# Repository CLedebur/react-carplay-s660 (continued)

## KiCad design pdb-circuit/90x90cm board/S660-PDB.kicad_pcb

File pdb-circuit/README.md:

# KiCad MCP workflow

Open the repository root in VS Code. The local `.vscode/mcp.json` connects
GitHub Copilot Agent mode to the separately installed KiCAD MCP server.
Use **MCP: List Servers** in the Command Palette to start `KiCAD-MCP-Server`
and confirm its tools are available, accepting VS Code's trust prompt if shown.

For a new checkout, copy `.vscode/mcp.example.json` to `.vscode/mcp.json`.
The example assumes the built `KiCAD-MCP-Server` repository is a sibling of
this repository and uses macOS KiCad Python paths. Adjust the Node command,
server entrypoint, `KICAD_PYTHON`, and `PYTHONPATH` to match your installation.
The active configuration is ignored by Git; the example is shared.

The local setup uses `.venv-kicad`, created with KiCad's bundled Python and
`--system-site-packages` so it can import `pcbnew`. To recreate it on macOS:

```bash
/Applications/KiCad/KiCad.app/Contents/Frameworks/Python.framework/Versions/Current/bin/python3 -m venv --system-site-packages .venv-kicad
.venv-kicad/bin/python3 -m pip install -r ../KiCAD-MCP-Server/requirements.txt
```

Set `KICAD_PYTHON` in your local `.vscode/mcp.json` to
`${workspaceFolder}/.venv-kicad/bin/python3` when using this environment.

Setup reference:
[KiCAD MCP Server — GitHub Copilot (VS Code)](https://github.com/mixelpixx/KiCAD-MCP-Server/blob/main/README.md#github-copilot-vs-code).

## Existing designs

Specify the exact design before asking the assistant to open or edit it:

| Directory | Project | Board | Schematic |
| --- | --- | --- | --- |
| `90x90cm board` | `S660-PDB.kicad_pro` | `S660-PDB.kicad_pcb` | `S660-PDB.kicad_sch` |
| `109x49cm board` | `S660-PCB-long.kicad_pro` | `S660-PCB-long.kicad_pcb` | `S660-PCB-long.kicad_sch` |
| `smt board` | `S660-PCB-long.kicad_pro` | `S660-PCB-long.kicad_pcb` | `S660-PCB-long.kicad_sch` |
| `smt board` | `S660-PCB-SMT-two-sided.kicad_pro` | `S660-PCB-SMT-two-sided.kicad_pcb` | No matching schematic file |

Example first prompt:

> Use the KiCad MCP tools to open `pdb-circuit/90x90cm board/S660-PDB.kicad_pro`
> with its absolute workspace path. Inspect the board and summarize its
> components, dimensions, and design-rule violations without changing it.

Discover available operations with `search_tools` or `get_category_tools`
before selecting a tool. Open and inspect the chosen design, create a checkpoint
before substantial changes, then save and run the relevant schematic ERC or PCB
DRC checks. Review any unresolved violations before exporting manufacturing files.
Coordinate file edits with the MCP session: close the project before editing its
files externally, then reopen it to avoid saving stale in-memory state.

The configuration leaves automatic GUI launch and development session logging
disabled. To use live PCB interaction, launch KiCad yourself and enable its IPC
API server in Preferences > Plugins. File-based operation does not require the GUI.

This VS Code configuration applies to Copilot. Other MCP clients need their own
server registration; it does not register tools in an already running Codex task.

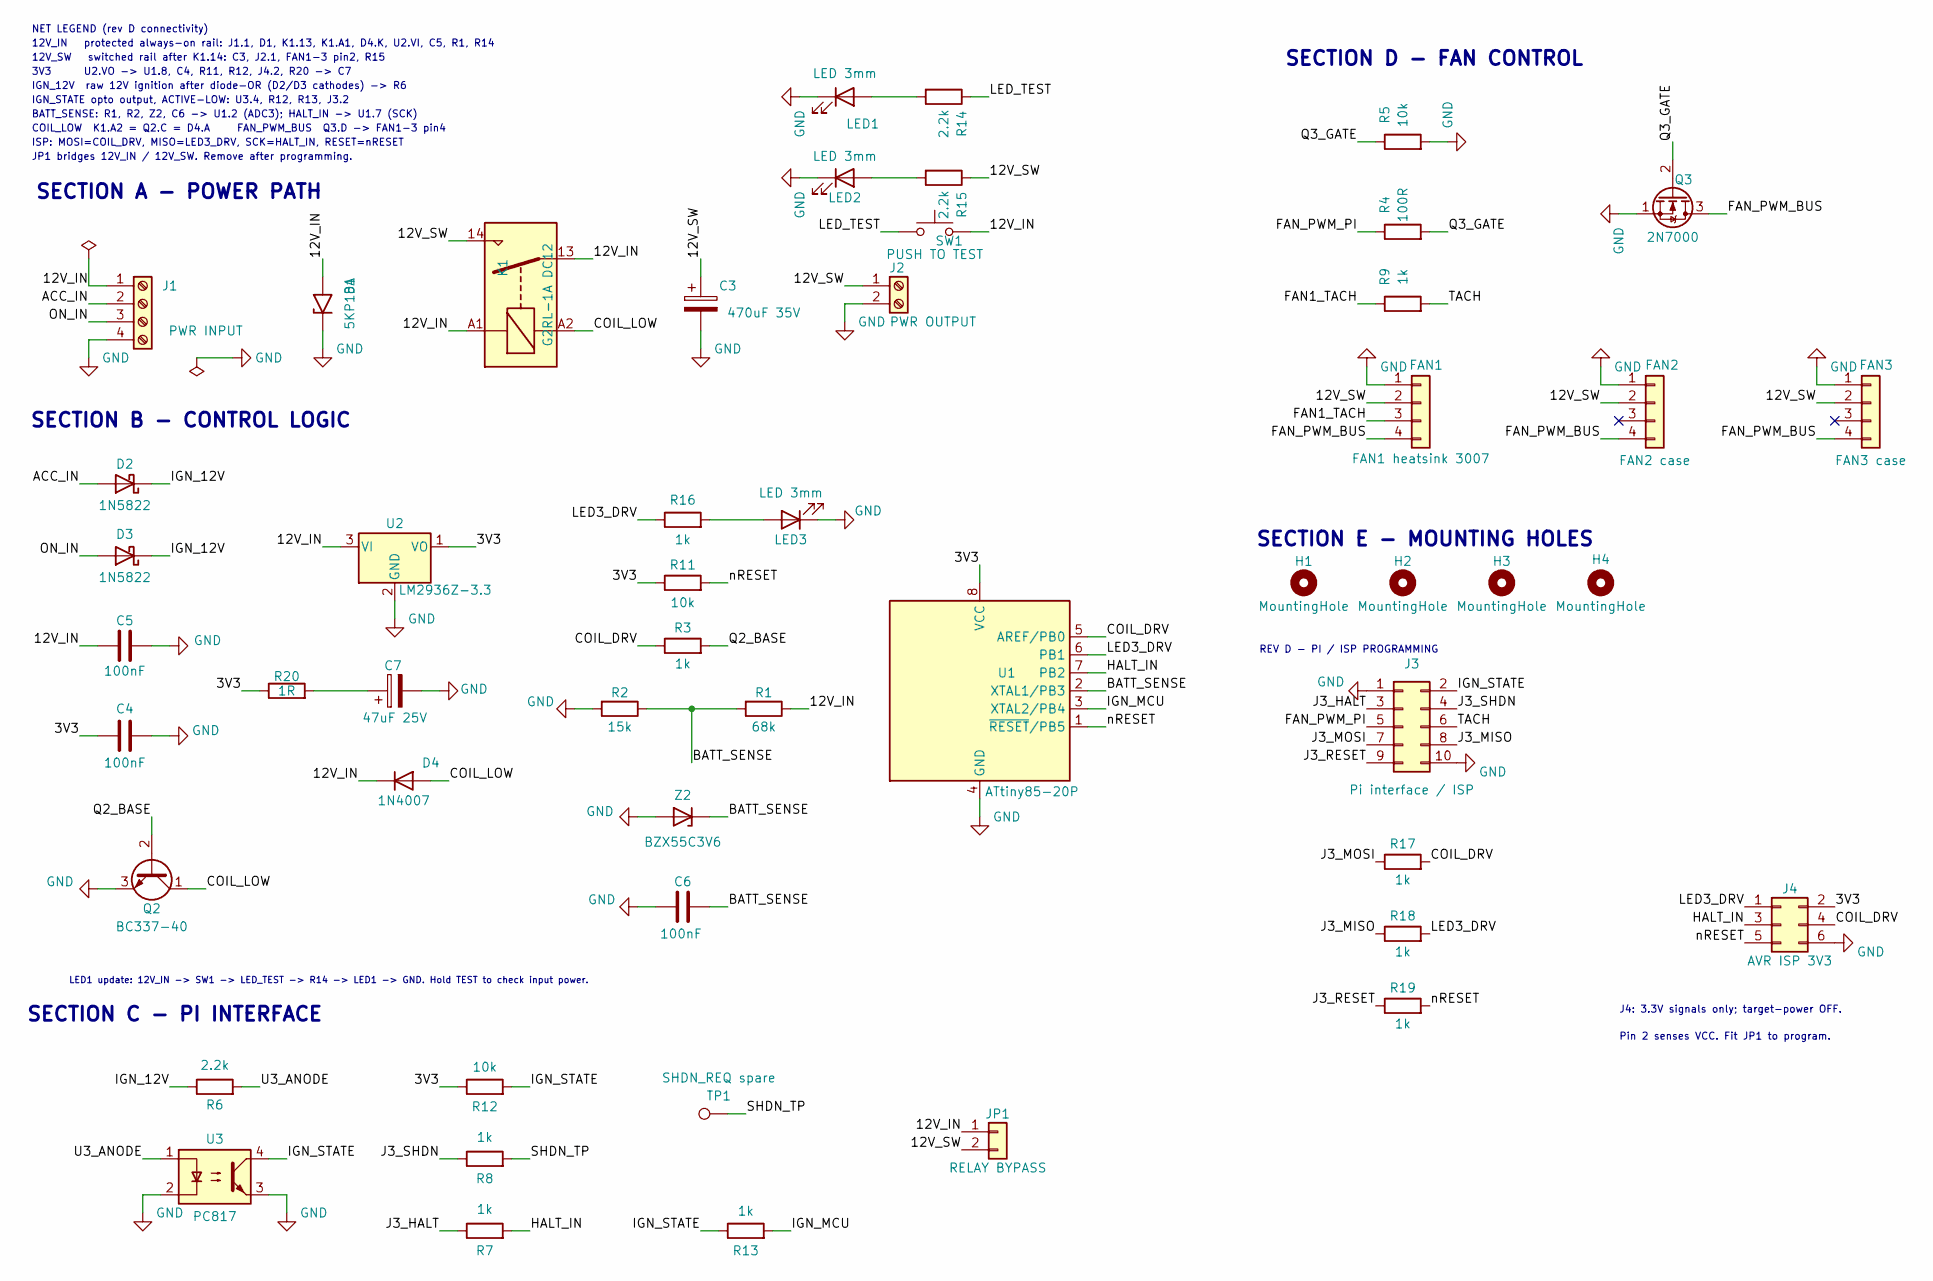
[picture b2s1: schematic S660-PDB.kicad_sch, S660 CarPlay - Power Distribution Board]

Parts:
C3: 470uF 35V; CP_Radial_D10.0mm_P5.00mm; MPN EEUFR1V471; LCSC C178715
C4, C5, C6: 100nF; C_Disc_D5.0mm_W2.5mm_P5.00mm; MPN FG28X7R1H104KNT00; LCSC C448595
C7: 47uF 25V; CP_Radial_D5.0mm_P2.00mm; MPN EEUFR1E470; LCSC C407893
D1: 5KP18A; D_P600_R-6_P20.00mm_Horizontal; MPN 5KP18A
D2, D3: 1N5822; D_Multicomp_1N5822_DO27_P15.24mm; MPN 1N5822; Farnell 4050109
D4: 1N4007; D_DO-41_SOD81_P10.16mm_Horizontal; MPN 1N4007-E3/54
FAN1: FAN1 heatsink 3007; PinHeader_1x04_P2.54mm_Vertical; MPN TSW-104-07-G-S
FAN2: FAN2 case; PinHeader_1x04_P2.54mm_Vertical; MPN TSW-104-07-G-S
FAN3: FAN3 case; PinHeader_1x04_P2.54mm_Vertical; MPN TSW-104-07-G-S
H1, H2, H3, H4: MountingHole; MountingHole_3.2mm_M3
J1: PWR INPUT; PhoenixContact_MC_1,5_4-G-5.08_1x04_P5.08mm_Horizontal; MPN 1836202; LCSC C5444352
J2: PWR OUTPUT; PhoenixContact_MC_1,5_2-G-5.08_1x02_P5.08mm_Horizontal; MPN 1836189; LCSC C5355140
J3: Pi interface / ISP; PinHeader_2x05_P2.54mm_Vertical; MPN TSW-105-07-G-D
J4: AVR ISP 3V3; PinHeader_2x03_P2.54mm_Vertical; MPN TSW-103-07-G-D
JP1: RELAY BYPASS; Phoenix_MKDS_1_2_3.5_1751248; MPN 1751248; LCSC C89122
K1: G2RL-1A DC12; Relay_SPST_Omron_G2RL-1A; MPN G2RL-1A DC12; LCSC C1524657
LED1, LED2, LED3: LED 3mm; LED_D3.0mm; MPN WP3A8ID
Q2: BC337-40; TO-92_Inline_Wide; MPN BC337-40
Q3: 2N7000; TO-92_Inline_Wide; MPN 2N7000
R1: 68k; R_Axial_DIN0207_L6.3mm_D2.5mm_P10.16mm_Horizontal; MPN MFR-25FBF52-68K
R2: 15k; R_Axial_DIN0207_L6.3mm_D2.5mm_P10.16mm_Horizontal; MPN MFR-25FBF52-15K; LCSC C3556390
R3, R7, R8, R9, R13, R16, R17, R18, R19: 1k; R_Axial_DIN0207_L6.3mm_D2.5mm_P10.16mm_Horizontal; MPN MFR-25FBF52-1K; LCSC C1364484
R4: 100R; R_Axial_DIN0207_L6.3mm_D2.5mm_P10.16mm_Horizontal; MPN MFR-25FBF52-100R
R5, R11, R12: 10k; R_Axial_DIN0207_L6.3mm_D2.5mm_P10.16mm_Horizontal; MPN MFR-25FBF52-10K; LCSC C1519255
R6, R14, R15: 2.2k; R_Axial_DIN0207_L6.3mm_D2.5mm_P10.16mm_Horizontal; MPN MFR-25FBF52-2K2
R20: 1R; R_Axial_DIN0207_L6.3mm_D2.5mm_P10.16mm_Horizontal; Power Rating 0.6W; Tolerance 1%; MPN MRS25000C1008FCT00
SW1: PUSH TO TEST; SW_PUSH_6mm_H4.3mm; MPN B3F-1000; LCSC C93157
TP1: SHDN_REQ spare; TestPoint_Pad_D1.5mm
U1: ATtiny85-20P; DIP-8_W7.62mm; MPN ATTINY85-20PU; LCSC C965497
U2: LM2936Z-3.3; TO-92_Inline_Wide; MPN LM2936Z-3.3/NOPB
U3: PC817; DIP-4_W7.62mm; MPN ISP817X
Z2: BZX55C3V6; D_DO-35_SOD27_P7.62mm_Horizontal; MPN BZX55C3V6-TAP

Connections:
/3V3: C4.1, J4.2, R11.1, R12.1, R20.1, U1.8 (VCC), U2.1 (VO)
/12V_SW: C3.1, FAN1.2, FAN2.2, FAN3.2, J2.1, JP1.2, K1.14, R15.1
/ACC_IN: D2.2 (A), J1.2
/BATT_SENSE: C6.1, R1.2, R2.1, U1.2 (XTAL1/PB3), Z2.1 (K)
/COIL_DRV: J4.4, R3.1, R17.2, U1.5 (AREF/PB0)
/COIL_LOW: D4.2 (A), K1.A2, Q2.1 (C)
/FAN1_TACH: FAN1.3, R9.1
/FAN_PWM_BUS: FAN1.4, FAN2.4, FAN3.4, Q3.3 (D)
/FAN_PWM_PI: J3.5, R4.1
/HALT_IN: J4.3, R7.2, U1.7 (PB2)
/IGN_12V: D2.1 (K), D3.1 (K), R6.1
/IGN_MCU: R13.2, U1.3 (XTAL2/PB4)
/IGN_STATE: J3.2, R12.2, R13.1, U3.4
/J3_HALT: J3.3, R7.1
/J3_MISO: J3.8, R18.1
/J3_MOSI: J3.7, R17.1
/J3_RESET: J3.9, R19.1
/J3_SHDN: J3.4, R8.1
/LED3_DRV: J4.1, R16.1, R18.2, U1.6 (PB1)
/LED_TEST: R14.1, SW1.1
/ON_IN: D3.2 (A), J1.3
/Q2_BASE: Q2.2 (B), R3.2
/Q3_GATE: Q3.2 (G), R4.2, R5.1
/SHDN_TP: R8.2, TP1.1 (1_1)
/TACH: J3.6, R9.2
/U3_ANODE: R6.2, U3.1
/nRESET: J4.5, R11.2, R19.2, U1.1 (~RESET/PB5)
unnamed: C7.1, R20.2
unnamed: LED1.2 (A), R14.2
unnamed: LED2.2 (A), R15.2
unnamed: LED3.2 (A), R16.2

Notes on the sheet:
REV D - PI / ISP PROGRAMMING
LED1 update: 12V_IN -> SW1 -> LED_TEST -> R14 -> LED1 -> GND. Hold TEST to check input power.
SECTION E - MOUNTING HOLES
JP1 bridges 12V_IN / 12V_SW. Remove after programming.
Pin 2 senses VCC. Fit JP1 to program.
SECTION C - PI INTERFACE
SECTION A - POWER PATH
SECTION D - FAN CONTROL
COIL_LOW K1.A2 = Q2.C = D4.A FAN_PWM_BUS Q3.D -> FAN1-3 pin4
ISP: MOSI=COIL_DRV, MISO=LED3_DRV, SCK=HALT_IN, RESET=nRESET
BATT_SENSE: R1, R2, Z2, C6 -> U1.2 (ADC3); HALT_IN -> U1.7 (SCK)
12V_SW switched rail after K1.14: C3, J2.1, FAN1-3 pin2, R15
12V_IN protected always-on rail: J1.1, D1, K1.13, K1.A1, D4.K, U2.VI, C5, R1, R14
NET LEGEND (rev D connectivity)
IGN_STATE opto output, ACTIVE-LOW: U3.4, R12, R13, J3.2
IGN_12V raw 12V ignition after diode-OR (D2/D3 cathodes) -> R6
SECTION B - CONTROL LOGIC
3V3 U2.VO -> U1.8, C4, R11, R12, J4.2, R20 -> C7
J4: 3.3V signals only; target-power OFF.

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
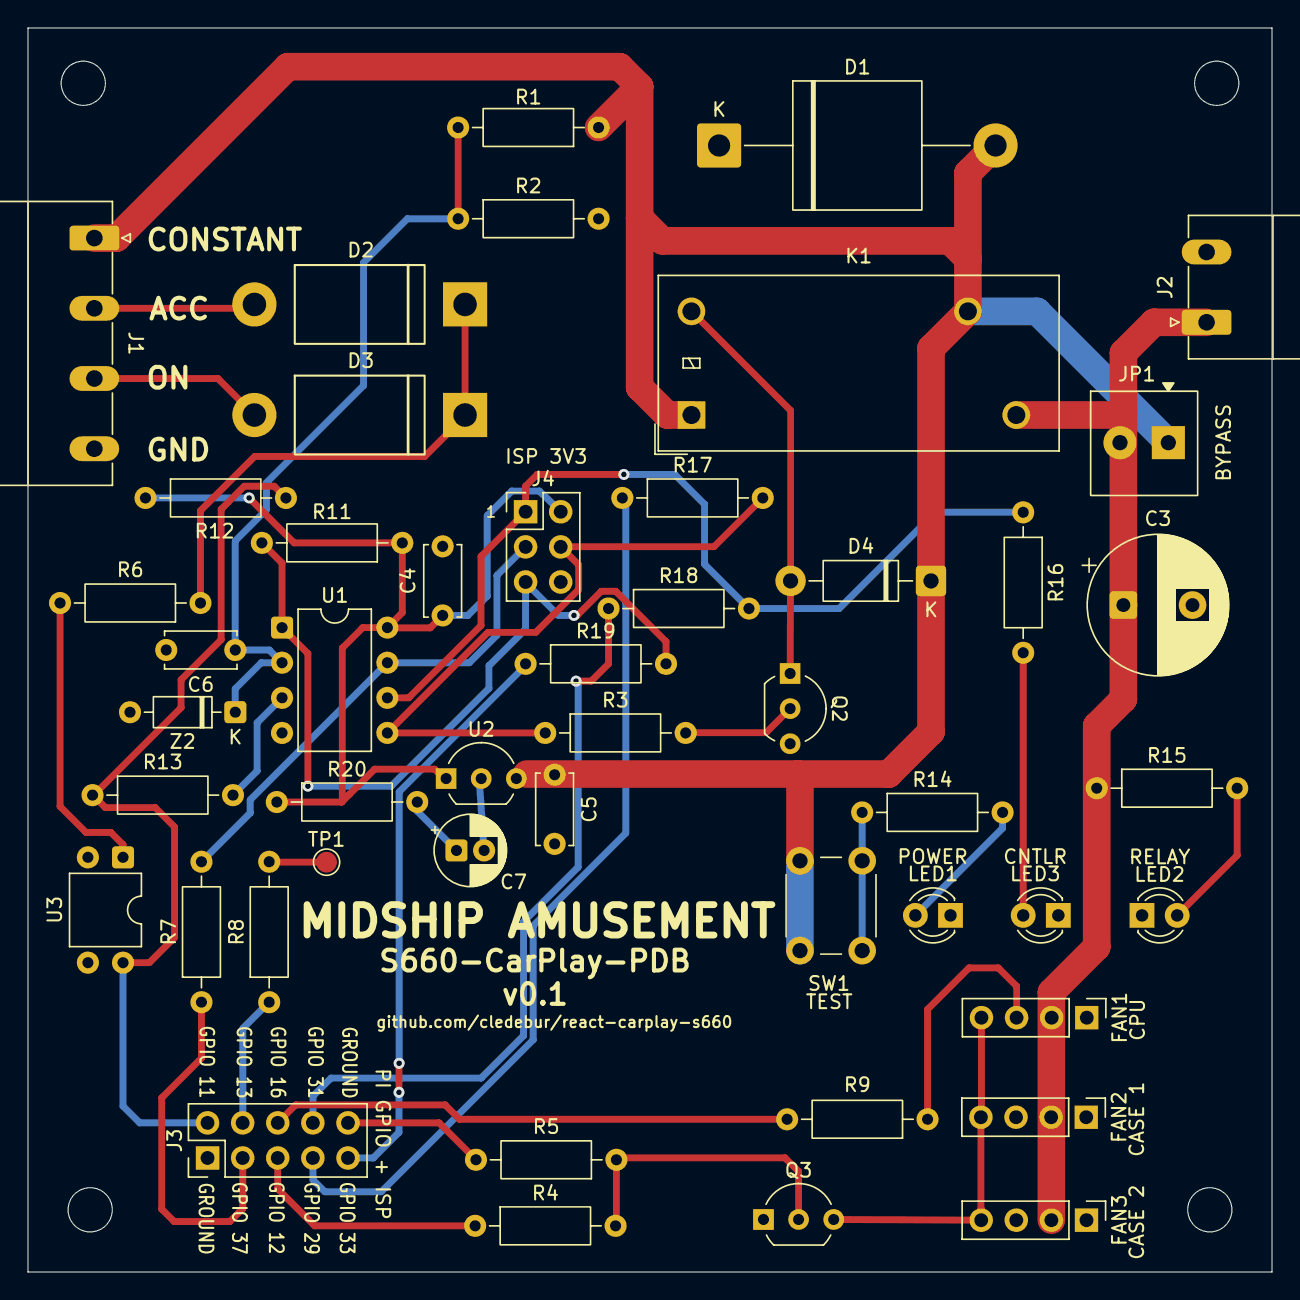
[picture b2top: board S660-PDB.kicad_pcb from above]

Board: 2 copper layers, 90.0 x 90.0 mm, 52 parts (0 on the bottom side), 33 nets.

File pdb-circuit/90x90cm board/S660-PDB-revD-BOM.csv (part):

"Reference","Value","Footprint","Manufacturer","MPN","Farnell","LCSC","QUANTITY","DNP","Assembly Manufacturer","Assembly MPN","Assembly LCSC","Assembly Notes","Datasheet","Socket Datasheet"
"C3","470uF 35V","Capacitor_THT:CP_Radial_D10.0mm_P5.00mm","Panasonic","EEUFR1V471","","C178715","1","","Panasonic","EEUFR1V471","C178715","10 mm diameter; 5 mm lead pitch. Do not substitute EEUFR1V471L.","https://industrial.panasonic.com/content/data/CP/PDF/S_Alm_A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",""
"C4","100nF","Capacitor_THT:C_Disc_D5.0mm_W2.5mm_P5.00mm","TDK","FG28X7R1H104KNT00","","C448595","1","","TDK","FG28X7R1H104KNT00","C448595","100 nF 50 V X7R 10%; radial 5 mm pitch.","https://product.tdk.com/en/search/capacitor/ceramic/lead-mlc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",""
"C5","100nF","Capacitor_THT:C_Disc_D5.0mm_W2.5mm_P5.00mm","TDK","FG28X7R1H104KNT00","","C448595","1","","TDK","FG28X7R1H104KNT00","C448595","100 nF 50 V X7R 10%; radial 5 mm pitch.","https://product.tdk.com/en/search/capacitor/ceramic/lead-mlc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",""
"C6","100nF","Capacitor_THT:C_Disc_D5.0mm_W2.5mm_P5.00mm","TDK","FG28X7R1H104KNT00","","C448595","1","","TDK","FG28X7R1H104KNT00","C448595","100 nF 50 V X7R 10%; radial 5 mm pitch.","https://product.tdk.com/en/search/capacitor/ceramic/lead-mlc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",""
"C7","47uF 25V","Capacitor_THT:CP_Radial_D5.0mm_P2.00mm","Panasonic","EEUFR1E470","","C407893","1","","Panasonic","EEUFR1E470","C407893","","https://industrial.panasonic.com/cdbs/www-data/pdf/RDF0000/A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",""
"D1","5KP18A","Diode_THT:D_P600_R-6_P20.00mm_Horizontal","Diotec Semiconductor","5KP18A","","","1","","Diotec Semiconductor","5KP18A","","","https://diotec.com/tl_files/diotec/files/pdf/datasheets/5kp65.pdf",""
"D2","1N5822","S660-PDB:D_Multicomp_1N5822_DO27_P15.24mm","Multicomp Pro","1N5822","4050109","","1","","Multicomp Pro","1N5822","","Exact Farnell 4050109 DO-27 package; do not substitute DO-201 without footprint review.","https://www.farnell.com/datasheets/3750001.pdf",""
"D3","1N5822","S660-PDB:D_Multicomp_1N5822_DO27_P15.24mm","Multicomp Pro","1N5822","4050109","","1","","Multicomp Pro","1N5822","","Exact Farnell 4050109 DO-27 package; do not substitute DO-201 without footprint review.","https://www.farnell.com/datasheets/3750001.pdf",""
"D4","1N4007","Diode_THT:D_DO-41_SOD81_P10.16mm_Horizontal","Vishay","1N4007-E3/54","","","1","","Vishay","1N4007-E3/54","","","https://www.vishay.com/docs/88503/1n4001.pdf",""
"FAN1","FAN1 heatsink 3007","Connector_PinHeader_2.54mm:PinHeader_1x04_P2.54mm_Vertical","Samtec","TSW-104-07-G-S","","","1","","Samtec","TSW-104-07-G-S","","Fit male 1x4 header, not a fan. Verify finished-hole fit with assembler.","https://suddendocs.samtec.com/prints/tsw-xxx-xx-xxx-x-xx-xxx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",""
"FAN2","FAN2 case","Connector_PinHeader_2.54mm:PinHeader_1x04_P2.54mm_Vertical","Samtec","TSW-104-07-G-S","","","1","","Samtec","TSW-104-07-G-S","","Fit male 1x4 header, not a fan. Verify finished-hole fit with assembler.","https://suddendocs.samtec.com/prints/tsw-xxx-xx-xxx-x-xx-xxx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",""
"FAN3","FAN3 case","Connector_PinHeader_2.54mm:PinHeader_1x04_P2.54mm_Vertical","Samtec","TSW-104-07-G-S","","","1","","Samtec","TSW-104-07-G-S","","Fit male 1x4 header, not a fan. Verify finished-hole fit with assembler.","https://suddendocs.samtec.com/prints/tsw-xxx-xx-xxx-x-xx-xxx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",""
"H1","MountingHole","MountingHole:MountingHole_3.2mm_M3","","","","","1","","","","","","",""
"H2","MountingHole","MountingHole:MountingHole_3.2mm_M3","","","","","1","","","","","","",""
"H3","MountingHole","MountingHole:MountingHole_3.2mm_M3","","","","","1","","","","","","",""
"H4","MountingHole","MountingHole:MountingHole_3.2mm_M3","","","","","1","","","","","","",""
"J1","PWR INPUT","Connector_Phoenix_MC_HighVoltage:PhoenixContact_MC_1,5_4-G-5.08_1x04_P5.08mm_Horizontal","Phoenix Contact","1836202","","C5444352","1","","Phoenix Contact","1836202","C5444352","PCB header only; mating cable plug not included.","",""
"J2","PWR OUTPUT","Connector_Phoenix_MC_HighVoltage:PhoenixContact_MC_1,5_2-G-5.08_1x02_P5.08mm_Horizontal","Phoenix Contact","1836189","","C5355140","1","","Phoenix Contact","1836189","C5355140","PCB header only; mating cable plug not included.","",""
"J3","Pi interface / ISP","Connector_PinHeader_2.54mm:PinHeader_2x05_P2.54mm_Vertical","Samtec","TSW-105-07-G-D","","","1","","Samtec","TSW-105-07-G-D","","Male 2x5 header; verify finished-hole fit with assembler.","https://suddendocs.samtec.com/prints/tsw-xxx-xx-xxx-x-xx-xxx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",""
"J4","AVR ISP 3V3","Connector_PinHeader_2.54mm:PinHeader_2x03_P2.54mm_Vertical","Samtec","TSW-103-07-G-D","","","1","","Samtec","TSW-103-07-G-D","","Male 2x3 header; verify finished-hole fit with assembler.","https://suddendocs.samtec.com/prints/tsw-xxx-xx-xxx-x-xx-xxx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",""
"JP1","RELAY BYPASS","S660-PDB:Phoenix_MKDS_1_2_3.5_1751248","Phoenix Contact","1751248","","C89122","1","","Phoenix Contact","1751248","C89122","Fit terminal block. Leave OPEN: no bypass wire or short.","https://www.farnell.com/datasheets/2322647.pdf",""
"K1","G2RL-1A DC12","Relay_THT:Relay_SPST_Omron_G2RL-1A","Omron","G2RL-1A DC12","","C1524657","1","","Omron","G2RL-1A DC12","C1524657","","https://components.omron.com/sites/default/files/datasheet_p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",""
"LED1","LED 3mm","LED_THT:LED_D3.0mm","Kingbright","WP3A8ID","","","1","","Kingbright","WP3A8ID","","Red 3 mm LED; pad 1 cathode.","https://www.kingbrightusa.com/images/catalog/SPEC/WP3A8ID.pdf",""
"LED2","LED 3mm","LED_THT:LED_D3.0mm","Kingbright","WP3A8ID","","","1","","Kingbright","WP3A8ID","","Red 3 mm LED; pad 1 cathode.","https://www.kingbrightusa.com/images/catalog/SPEC/WP3A8ID.pdf",""
"LED3","LED 3mm","LED_THT:LED_D3.0mm","Kingbright","WP3A8ID","","","1","","Kingbright","WP3A8ID","","Red 3 mm LED; pad 1 cathode.","https://www.kingbrightusa.com/images/catalog/SPEC/WP3A8ID.pdf",""
"Q2","BC337-40","Package_TO_SOT_THT:TO-92_Inline_Wide","Diotec Semiconductor","BC337-40","","","1","","Diotec Semiconductor","BC337-40","","Pads 1 C, 2 B, 3 E. 2.54 mm pitch; confirm lead forming.","https://diotec.com/tl_files/diotec/files/pdf/datasheets/bc337.pdf",""
"Q3","2N7000","Package_TO_SOT_THT:TO-92_Inline_Wide","Diotec Semiconductor","2N7000","","","1","","Diotec Semiconductor","2N7000","","Pads 1 S, 2 G, 3 D. 2.54 mm pitch.","https://diotec.com/tl_files/diotec/files/pdf/datasheets/2n7000.pdf",""
"R1","68k","Resistor_THT:R_Axial_DIN0207_L6.3mm_D2.5mm_P10.16mm_Horizontal","Yageo","MFR-25FBF52-68K","","","1","","Yageo","MFR-25FBF52-68K","","1%, 0.25 W; form axial leads to 10.16 mm.","https://yageogroup.com/content/datasheet/asset/file/YAGEO-MF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",""
"R2","15k","Resistor_THT:R_Axial_DIN0207_L6.3mm_D2.5mm_P10.16mm_Horizontal","Yageo","MFR-25FBF52-15K","","C3556390","1","","Yageo","MFR-25FBF52-15K","C3556390","1%, 0.25 W; form axial leads to 10.16 mm.","https://yageogroup.com/content/datasheet/asset/file/YAGEO-MF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",""
"R3","1k","Resistor_THT:R_Axial_DIN0207_L6.3mm_D2.5mm_P10.16mm_Horizontal","Yageo","MFR-25FBF52-1K","","C1364484","1","","Yageo","MFR-25FBF52-1K","C1364484","1%, 0.25 W; form axial leads to 10.16 mm.","https://yageogroup.com/content/datasheet/asset/file/YAGEO-MF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",""
"R4","100R","Resistor_THT:R_Axial_DIN0207_L6.3mm_D2.5mm_P10.16mm_Horizontal","Yageo","MFR-25FBF52-100R","","","1","","Yageo","MFR-25FBF52-100R","","1%, 0.25 W; form axial leads to 10.16 mm.","https://yageogroup.com/content/datasheet/asset/file/YAGEO-MF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",""
"R5","10k","Resistor_THT:R_Axial_DIN0207_L6.3mm_D2.5mm_P10.16mm_Horizontal","Yageo","MFR-25FBF52-10K","","C1519255","1","","Yageo","MFR-25FBF52-10K","C1519255","1%, 0.25 W; form axial leads to 10.16 mm.","https://yageogroup.com/content/datasheet/asset/file/YAGEO-MF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",""
"R6","2.2k","Resistor_THT:R_Axial_DIN0207_L6.3mm_D2.5mm_P10.16mm_Horizontal","Yageo","MFR-25FBF52-2K2","","","1","","Yageo","MFR-25FBF52-2K2","","1%, 0.25 W; form axial leads to 10.16 mm.","https://yageogroup.com/content/datasheet/asset/file/YAGEO-MF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",""
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
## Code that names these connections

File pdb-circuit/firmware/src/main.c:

// S660-PDB power supervisor — ATtiny85 (U1 on the PDB boards, U101 on the Buddy Board).
// Hardware glue only; the behaviour is the state machine in pdb.c.
//
// Pins (rev D, PDB reference §5 / §9.1):
//   PB0  pin 5  COIL_DRV   out  HIGH = relay closed (also ISP MOSI)
//   PB1  pin 6  LED3_DRV   out  heartbeat LED (also ISP MISO)
//   PB2  pin 7  HALT_IN    in   HIGH = the Pi has halted (also ISP SCK)
//   PB3  pin 2  BATT_SENSE ADC3, 12V_IN × 15/83
//   PB4  pin 3  IGN_MCU    in   LOW = ACC or ON present; pin-change wake
//   PB5  pin 1  RESET      ISP only. Never set RSTDISBL.
//
// Clock: internal 8 MHz RC (lfuse 0xE2). The 10 ms tick is Timer0 in CTC mode. In RUN,
// GRACE, CUT and CYCLE the CPU idles between ticks; in SLEEP it powers down and only an
// ignition change wakes it. The watchdog resets a hung CPU while the relay can be closed.
#include <avr/io.h>
#include <avr/interrupt.h>
#include <avr/sleep.h>
#include <avr/wdt.h>
#include <avr/power.h>
#include "pdb.h"

#define PIN_COIL PB0
#define PIN_LED  PB1
#define PIN_HALT PB2
#define PIN_IGN  PB4

static volatile uint8_t ticks;

ISR(TIM0_COMPA_vect) { ticks++; }
EMPTY_INTERRUPT(PCINT0_vect)   // only here to wake from power-down

// A watchdog reset leaves WDRF set, which keeps the watchdog running at its shortest
// timeout; clear it before main() so a reset can't turn into a reset loop.
void wdt_early_off(void) __attribute__((naked, used, section(".init3")));
void wdt_early_off(void) { MCUSR = 0; wdt_disable(); }

static uint16_t batt_read(void) {
    uint16_t sum = 0;
    for (uint8_t i = 0; i < 4; i++) {
        ADCSRA |= _BV(ADSC);
        while (ADCSRA & _BV(ADSC)) {}
        sum += ADC;
    }
    return sum / 4;
}

static void read_inputs(pdb_inputs_t *in) {
    uint8_t pins = PINB;
    in->ign_on = !(pins & _BV(PIN_IGN));
    in->halt = pins & _BV(PIN_HALT);
    in->batt_adc = batt_read();
}

static void outputs(bool relay, bool led) {
    uint8_t o = PORTB & ~(_BV(PIN_COIL) | _BV(PIN_LED));
    if (relay) o |= _BV(PIN_COIL);
    if (led) o |= _BV(PIN_LED);
    PORTB = o;
}

static void power_down(void) {
    outputs(false, false);
    ADCSRA &= ~_BV(ADEN);
    wdt_disable();
    set_sleep_mode(SLEEP_MODE_PWR_DOWN);
    cli();
    if (PINB & _BV(PIN_IGN)) {   // ignition still off: sleep (re-checked with interrupts off)
        sleep_enable();
#ifdef sleep_bod_disable
        sleep_bod_disable();     // BOD off while asleep saves ~20 µA
#endif
        sei();
        sleep_cpu();
        sleep_disable();
    }
    sei();
    ADCSRA |= _BV(ADEN);
    wdt_enable(WDTO_1S);
    ticks = 0;
}

int main(void) {
    clock_prescale_set(clock_div_1);   // 8 MHz even if the CKDIV8 fuse is still set
    power_timer1_disable();
    power_usi_disable();

    DDRB = _BV(PIN_COIL) | _BV(PIN_LED);
    PORTB = 0;                         // outputs low, inputs without pull-ups (both have
                                       // external pulls: R112 on IGN, the Pi on HALT)
    DIDR0 = _BV(ADC3D);
    ADMUX = 3;                         // ADC3, VCC reference
    ADCSRA = _BV(ADEN) | _BV(ADPS2) | _BV(ADPS1);   // 8 MHz / 64 = 125 kHz

    TCCR0A = _BV(WGM01);               // CTC
    OCR0A = 77;                        // 8 MHz / 1024 / 78 = 100.16 Hz
    TCCR0B = _BV(CS02) | _BV(CS00);
    TIMSK = _BV(OCIE0A);

    PCMSK = _BV(PCINT4);
    GIMSK = _BV(PCIE);

    pdb_t p;
    pdb_inputs_t in;
    read_inputs(&in);
    pdb_init(&p, in.ign_on);
    outputs(pdb_relay(&p), pdb_led(&p));

    wdt_enable(WDTO_1S);
    sei();

    for (;;) {
        while (ticks) {
            cli(); ticks--; sei();
            read_inputs(&in);
            pdb_tick(&p, &in, PDB_TICK_MS);
            outputs(pdb_relay(&p), pdb_led(&p));
        }
        wdt_reset();
        if (pdb_can_power_down(&p) && (PINB & _BV(PIN_IGN))) {
            power_down();
        } else {
            set_sleep_mode(SLEEP_MODE_IDLE);
            sleep_mode();
        }
    }
}

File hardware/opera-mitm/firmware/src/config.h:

// Pin map and tunables. Matches hardware/opera-mitm/tap-board.md ("Pico pin map").
#pragma once

// Inputs
#define PIN_PW_IN     2    // PWR SW via 2N7000 buffer: HIGH = pressed (inverted)
#define PIN_TX_IN     5    // panel's OPERA TX (UART1 RX)
#define PIN_RX_IN    13    // head unit's OPERA RX line (UART0 RX) — also our "car is on" sense
#define PIN_CONT_ADC 26    // OPERA CONT via 68k/15k, ADC0

// Outputs (all drive 2N7000 gates: HIGH = line pulled low)
#define PIN_TX_OUT    4    // to head unit's OPERA TX input (UART1 TX, inverted at the pad)
#define PIN_PW_OUT    3    // to head unit's PWR SW input
#define PIN_RLY       6    // bypass relays (HIGH = energised = Pico in the path)
#define PIN_RST       7    // CM4 RUN_PG (HIGH = held in reset)
#define PIN_LED      22    // LED1 (GPIO25 is the Pico 2 W's wireless chip, so not the default LED pin)

#define OPERA_BAUD 19200

// Behaviour
#define PW_DEBOUNCE_MS       20
#define PW_HOLD_REBOOT_MS  3000   // hold Power this long → reset the CM4
#define RST_PULSE_MS        200
#define KNOB_KEY_PULSE_MS    25   // how long a knob click "presses" its key
#define RELAY_ENGAGE_MS    1500   // after boot, before the relays pull the Pico into the path
#define WATCHDOG_MS        2000
#define LED_BLINK_MS        500   // LED1 half-period in HEADUNIT mode
#define LED_FLICKER_MS       60   // LED1 inverted this long for each panel message
#define CONSOLE_LINE_MAX     16   // longest console command line

// HID keycodes for CarPlay mode (Chromium sees a plain USB keyboard).
// The web app maps these to CarPlay commands; keep them boring and unambiguous.
#define KEY_KNOB_CW    HID_KEY_ARROW_RIGHT
#define KEY_KNOB_CCW   HID_KEY_ARROW_LEFT
#define KEY_KNOB_PUSH  HID_KEY_ENTER
#define KEY_BACK       HID_KEY_ESCAPE
#define KEY_MODE       HID_KEY_M
#define KEY_PHONE      HID_KEY_P

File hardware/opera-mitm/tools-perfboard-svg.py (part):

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        out += ['## Solder bridges (flow solder across two neighbouring pads)', '']
        for a, b_ in self.bridges: out.append(f'- [ ] `{a}`–`{b_}`')
        out += ['', '## Off-board wires', '',
                '- [ ] Harness pin 1, **panel-side** wire → terminal **TXp** (B2)',
                '- [ ] Harness pin 1, **head-unit-side** wire → terminal **TXh** (D2)',
                '- [ ] Harness pin 2 (both wires still joined) → terminal **RX** (F2)',
                '- [ ] Harness pin 3, **panel-side** wire → terminal **PWp** (H2)',
                '- [ ] Harness pin 3, **head-unit-side** wire → terminal **PWh** (J2)',
                '- [ ] Harness pin 12 (both wires joined) → terminal **CONT** (L2)',
                '- [ ] Harness pin 9 → terminal **GND** (N2)',
                '- [ ] TOFU **J1 pin 3 (RUN_PG)** → terminal **RUN** (P2) — optional until the headers are in',
                '- [ ] TOFU **J1 pin 2 (GND)** → terminal **GND** (R2) — optional, goes with RUN',
                '- [ ] Pico USB → TOFU USB', '']
        return '\n'.join(out)

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    rows = [str(i) for i in range(1, 32)]        # the kit's 7 x 9 board: 26 x 31 holes
    b = Board(cols, rows, 'OPERA MITM — 7 × 9 cm perfboard (26 × 31 holes), component side. Pico 2 W plugs into the two 1×20 sockets at the bottom.')
    b.grid(top_letters=False)
    b.terminal('B', '2', ['TXp', 'TXh', 'RX', 'PWp', 'PWh', 'CONT', 'GND'], ['pin 1 panel', 'pin 1 HU', 'pin 2', 'pin 3 panel', 'pin 3 HU', 'pin 12', 'pin 9'])
    b.terminal('P', '2', ['RUN', 'GND'], ['J1 pin 3', 'J1 pin 2'])
    b.bus('A', 'Z', '13', GND, 'GND bus · bare wire, solder side')
    b.bus('A', 'Z', '21', VBUS, 'VBUS bus · bare wire, solder side')

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    b.wire('O', '12', 'L', '23', SIG, 'Pico pin 9 GP6 → Q3 gate resistor')
    b.wire('Z', '12', 'M', '23', SIG, 'Pico pin 10 GP7 → Q4 gate resistor')
    b.wire('E', '8', 'T', '23', SIG, 'RX junction → Pico pin 17 GP13')
    b.wire('N', '8', 'M', '30', SIG, 'CONT junction → Pico pin 31 GP26')
    for c1, c2, r in (('E', 'I', '15'), ('E', 'I', '18'), ('Q', 'U', '15'), ('Q', 'U', '18')):
        b.wire(c1, r, c2, r, LINK, f'TEMP: {"K1" if c1 == "E" else "K2"} COM-{"A" if r == "15" else "B"} → NO-{"A" if r == "15" else "B"} (remove when the relay is fitted)')

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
